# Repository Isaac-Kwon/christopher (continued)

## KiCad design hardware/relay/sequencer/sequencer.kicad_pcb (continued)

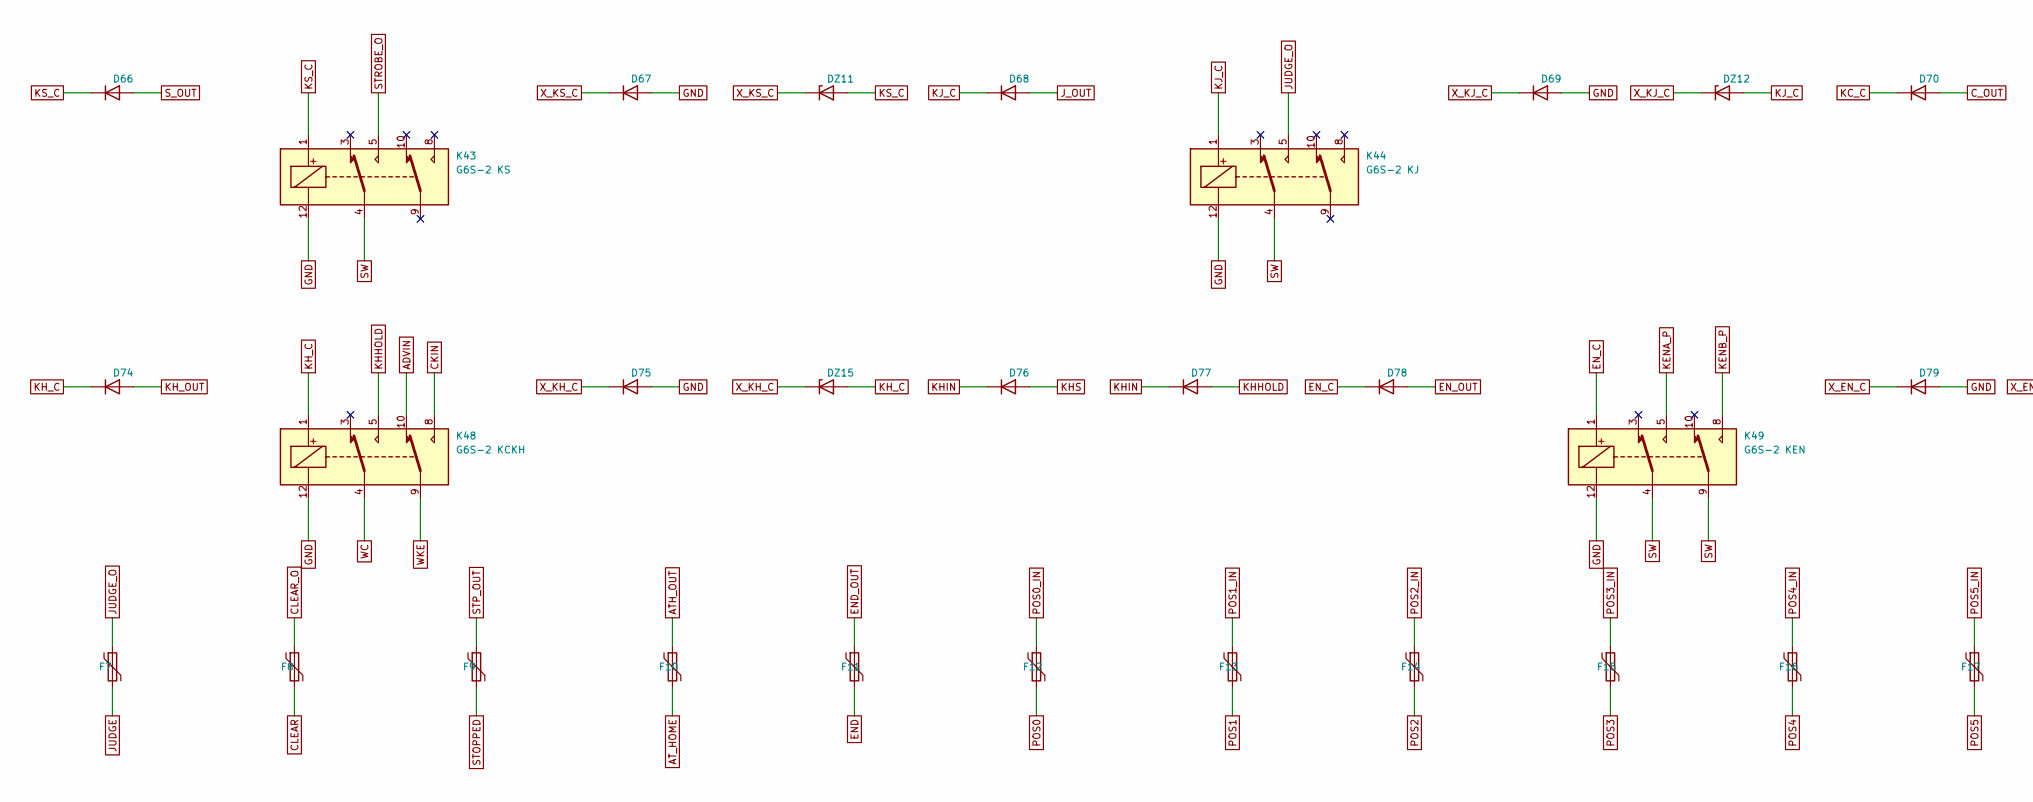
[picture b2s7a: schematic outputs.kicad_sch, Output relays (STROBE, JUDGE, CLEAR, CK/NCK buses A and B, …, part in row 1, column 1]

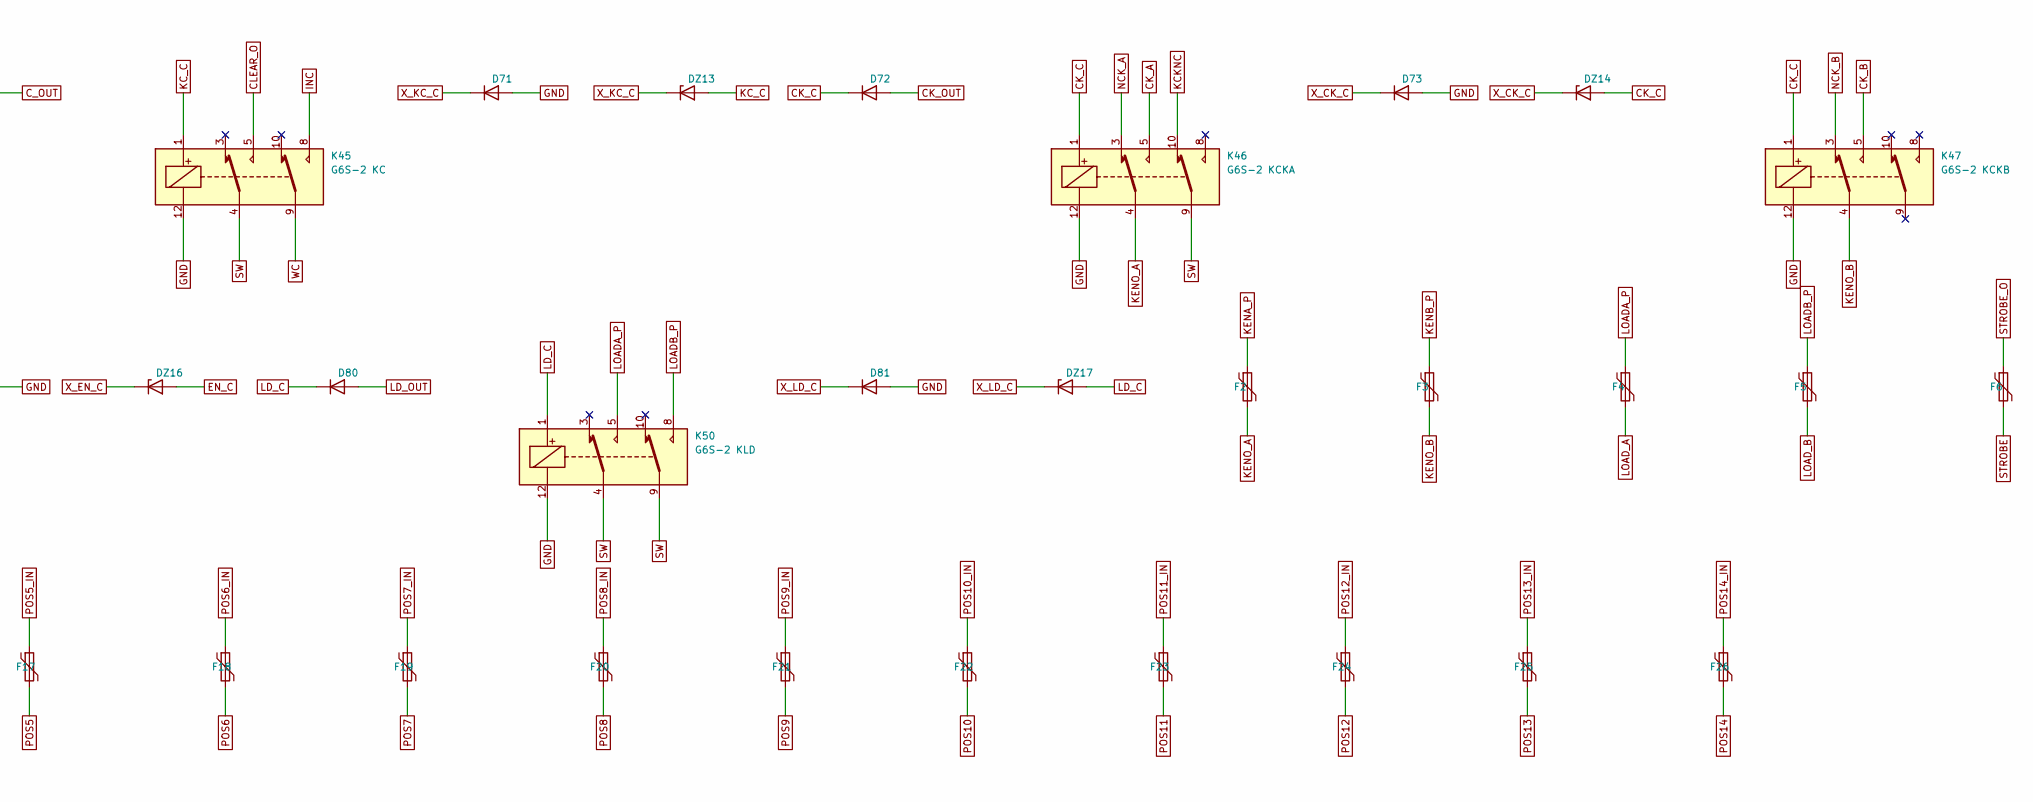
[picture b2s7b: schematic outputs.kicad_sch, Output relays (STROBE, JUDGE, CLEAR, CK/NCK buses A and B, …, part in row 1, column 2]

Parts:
D66, D67, D68, D69, D70, D71, D72, D73, D74, D75, D76, D77, D78, D79, D80, D81: 1N4148W; D_SOD-123
DZ11, DZ12, DZ13, DZ14, DZ15, DZ16, DZ17: BZT52C30; D_SOD-123
F2, F3: PTC 1.1A hold; Fuse_1812_4532Metric
F4, F5: PTC 0.1A hold; Fuse_1206_3216Metric
F6, F7, F8, F9, F10, F11, F12, F13, F14, F15, F16, F17, F18, F19, F20, F21, F22, F23, F24, F25, F26: PTC 30mA hold / 100mA trip; Fuse_1206_3216Metric
K43: G6S-2 KS; Relay_DPDT_Omron_G6S-2
K44: G6S-2 KJ; Relay_DPDT_Omron_G6S-2
K45: G6S-2 KC; Relay_DPDT_Omron_G6S-2
K46: G6S-2 KCKA; Relay_DPDT_Omron_G6S-2
K47: G6S-2 KCKB; Relay_DPDT_Omron_G6S-2
K48: G6S-2 KCKH; Relay_DPDT_Omron_G6S-2
K49: G6S-2 KEN; Relay_DPDT_Omron_G6S-2
K50: G6S-2 KLD; Relay_DPDT_Omron_G6S-2

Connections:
ADVIN: K48.10; also elsewhere on the board
ATH_OUT: F10.1; also elsewhere on the board
AT_HOME: F10.2; also elsewhere on the board
CKIN: K48.8; also elsewhere on the board
CK_A: K46.5; also elsewhere on the board
CK_B: K47.5; also elsewhere on the board
CK_C: D72.1 (K), DZ14.2 (A), K46.1, K47.1
CK_OUT: D72.2 (A); also elsewhere on the board
CLEAR: F8.2; also elsewhere on the board
CLEAR_O: F8.1, K45.5
C_OUT: D70.2 (A); also elsewhere on the board
END: F11.2; also elsewhere on the board
END_OUT: F11.1; also elsewhere on the board
EN_C: D78.1 (K), DZ16.2 (A), K49.1
EN_OUT: D78.2 (A); also elsewhere on the board
GND: D67.2 (A), D69.2 (A), D71.2 (A), D73.2 (A), D75.2 (A), D79.2 (A), D81.2 (A), K43.12, K44.12, K45.12, K46.12, K47.12, K48.12, K49.12, K50.12; also elsewhere on the board
INC: K45.8; also elsewhere on the board
JUDGE: F7.2; also elsewhere on the board
JUDGE_O: F7.1, K44.5
J_OUT: D68.2 (A); also elsewhere on the board
KCKNC: K46.10; also elsewhere on the board
KC_C: D70.1 (K), DZ13.2 (A), K45.1
KENA_P: F2.1, K49.5
KENB_P: F3.1, K49.8
KENO_A: F2.2, K46.4
KENO_B: F3.2, K47.4
KHHOLD: D77.2 (A), K48.5
KHIN: D76.1 (K), D77.1 (K); also elsewhere on the board
KHS: D76.2 (A); also elsewhere on the board
KH_C: D74.1 (K), DZ15.2 (A), K48.1
KH_OUT: D74.2 (A); also elsewhere on the board
KJ_C: D68.1 (K), DZ12.2 (A), K44.1
KS_C: D66.1 (K), DZ11.2 (A), K43.1
LD_C: D80.1 (K), DZ17.2 (A), K50.1
LD_OUT: D80.2 (A); also elsewhere on the board
LOADA_P: F4.1, K50.5
LOADB_P: F5.1, K50.8
LOAD_A: F4.2; also elsewhere on the board
LOAD_B: F5.2; also elsewhere on the board
NCK_A: K46.3; also elsewhere on the board
NCK_B: K47.3; also elsewhere on the board
POS0: F12.2; also elsewhere on the board
POS0_IN: F12.1; also elsewhere on the board
POS1: F13.2; also elsewhere on the board
POS1_IN: F13.1; also elsewhere on the board
POS2: F14.2; also elsewhere on the board
POS2_IN: F14.1; also elsewhere on the board
POS3: F15.2; also elsewhere on the board
POS3_IN: F15.1; also elsewhere on the board
POS4: F16.2; also elsewhere on the board
POS4_IN: F16.1; also elsewhere on the board
POS5: F17.2; also elsewhere on the board
POS5_IN: F17.1; also elsewhere on the board
POS6: F18.2; also elsewhere on the board
POS6_IN: F18.1; also elsewhere on the board
POS7: F19.2; also elsewhere on the board
POS7_IN: F19.1; also elsewhere on the board
POS8: F20.2; also elsewhere on the board
POS8_IN: F20.1; also elsewhere on the board
POS9: F21.2; also elsewhere on the board
POS9_IN: F21.1; also elsewhere on the board
POS10: F22.2; also elsewhere on the board
POS10_IN: F22.1; also elsewhere on the board
POS11: F23.2; also elsewhere on the board
POS11_IN: F23.1; also elsewhere on the board
POS12: F24.2; also elsewhere on the board
POS12_IN: F24.1; also elsewhere on the board
POS13: F25.2; also elsewhere on the board
POS13_IN: F25.1; also elsewhere on the board
POS14: F26.2; also elsewhere on the board
POS14_IN: F26.1; also elsewhere on the board
STOPPED: F9.2; also elsewhere on the board
STP_OUT: F9.1; also elsewhere on the board
STROBE: F6.2; also elsewhere on the board
STROBE_O: F6.1, K43.5
SW: K43.4, K44.4, K45.4, K46.9, K49.4, K49.9, K50.4, K50.9; also elsewhere on the board
S_OUT: D66.2 (A); also elsewhere on the board
WC: K45.9, K48.4; also elsewhere on the board
WKE: K48.9; also elsewhere on the board
X_CK_C: D73.1 (K), DZ14.1 (K)
X_EN_C: D79.1 (K), DZ16.1 (K)
X_KC_C: D71.1 (K), DZ13.1 (K)
X_KH_C: D75.1 (K), DZ15.1 (K)
X_KJ_C: D69.1 (K), DZ12.1 (K)
X_KS_C: D67.1 (K), DZ11.1 (K)
X_LD_C: D81.1 (K), DZ17.1 (K)

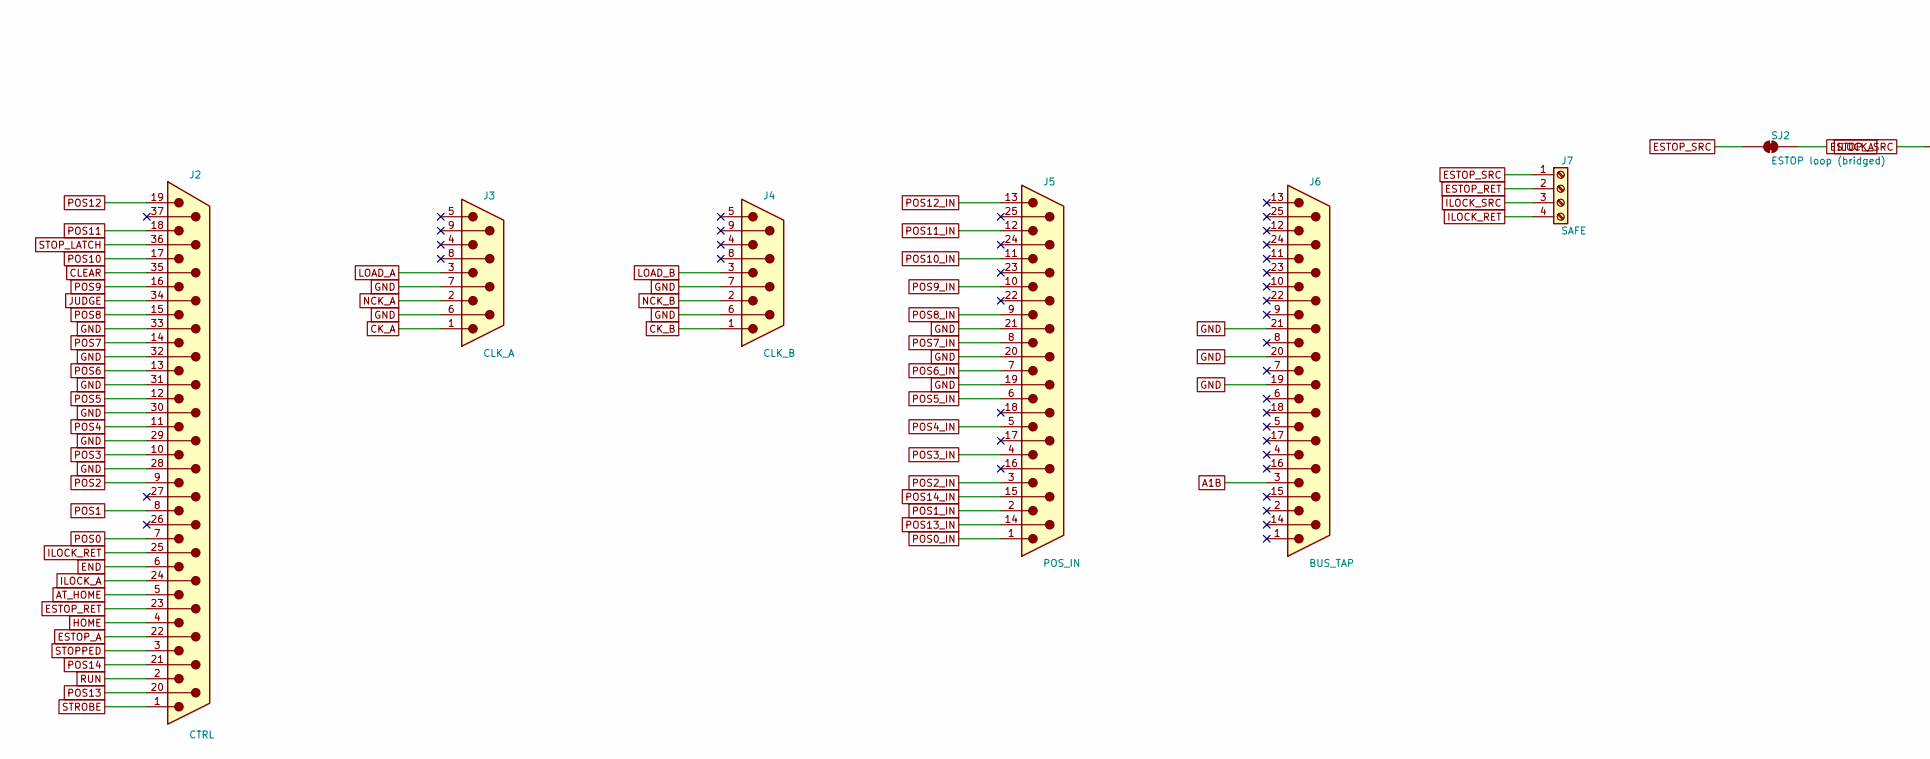
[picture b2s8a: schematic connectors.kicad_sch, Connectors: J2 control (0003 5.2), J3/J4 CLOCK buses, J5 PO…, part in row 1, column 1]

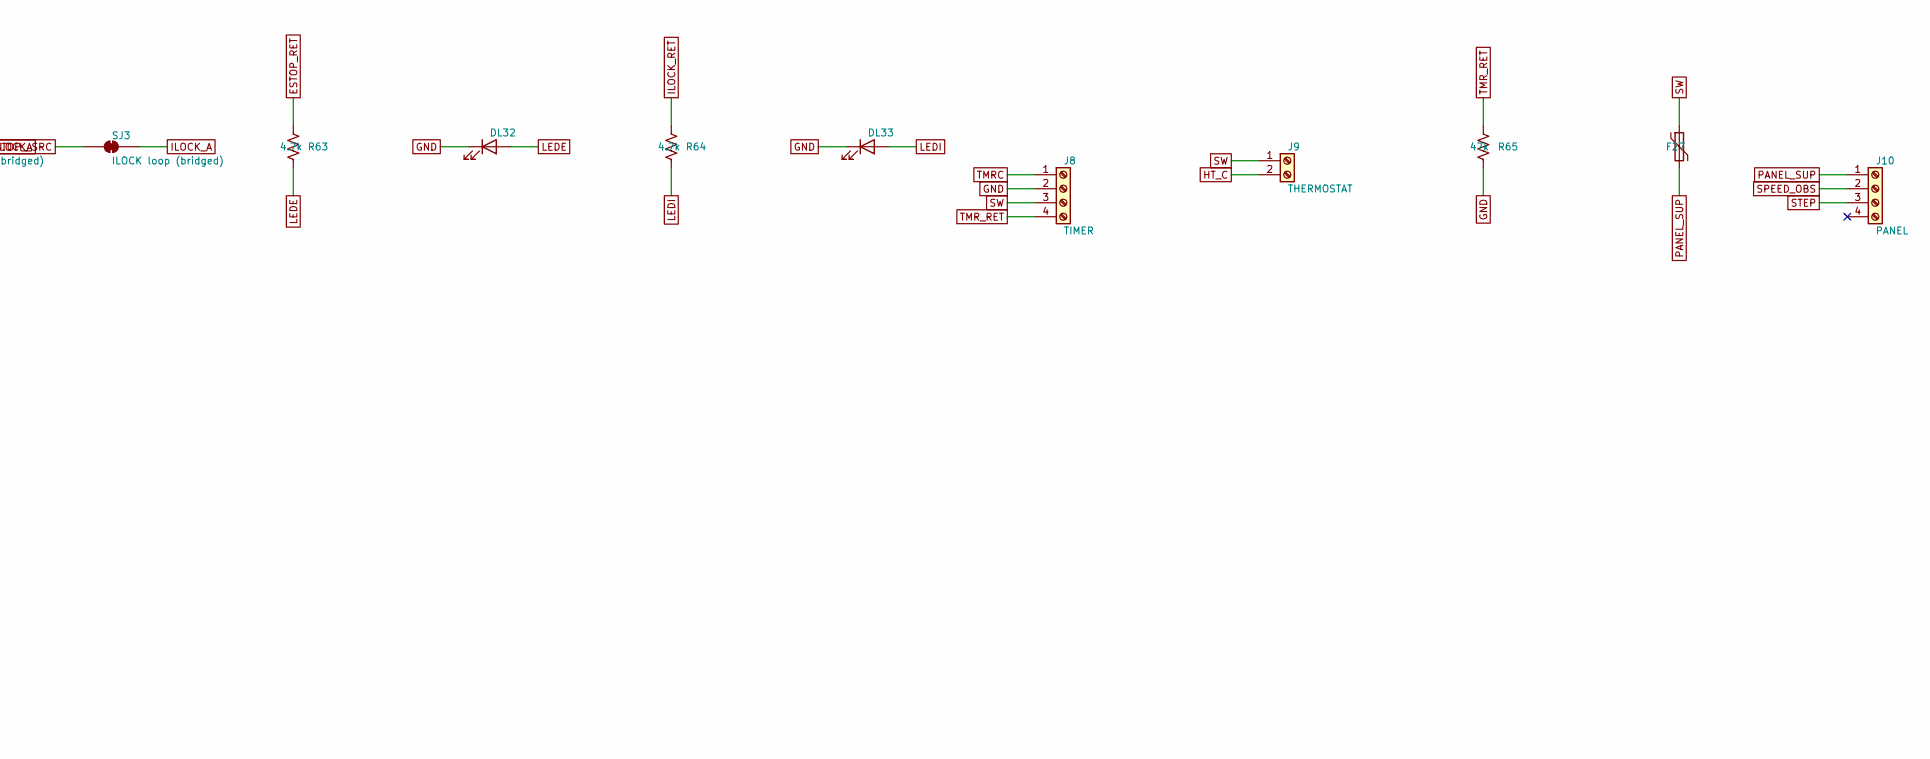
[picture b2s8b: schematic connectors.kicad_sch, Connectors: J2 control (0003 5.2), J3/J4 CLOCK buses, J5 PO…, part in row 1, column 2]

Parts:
DL32: ESTOP loop closed; LED_0603_1608Metric
DL33: ILOCK loop closed; LED_0603_1608Metric
F27: PTC 0.1A hold; Fuse_1206_3216Metric
J2: CTRL; DSUB-37_Pins_Horizontal_P2.77x2.84mm_EdgePinOffset9.90mm_Ho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
J3: CLK_A; DSUB-9_Pins_Horizontal_P2.77x2.84mm_EdgePinOffset9.90mm_Hou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
J4: CLK_B; DSUB-9_Pins_Horizontal_P2.77x2.84mm_EdgePinOffset9.90mm_Hou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
J5: POS_IN; DSUB-25_Pins_Horizontal_P2.77x2.84mm_EdgePinOffset9.90mm_Ho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
J6: BUS_TAP; DSUB-25_Pins_Horizontal_P2.77x2.84mm_EdgePinOffset9.90mm_Ho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
J7: SAFE; TerminalBlock_Phoenix_MKDS-1,5-4-5.08_1x04_P5.08mm_Horizont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
J8: TIMER; TerminalBlock_Phoenix_MKDS-1,5-4-5.08_1x04_P5.08mm_Horizont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
J9: THERMOSTAT; TerminalBlock_Phoenix_MKDS-1,5-2-5.08_1x02_P5.08mm_Horizont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
J10: PANEL; TerminalBlock_Phoenix_MKDS-1,5-4-5.08_1x04_P5.08mm_Horizont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
R63, R64: 4.7k; R_0603_1608Metric
R65: 47k; R_0603_1608Metric
SJ2: ESTOP loop (bridged); SolderJumper-2_P1.3mm_Bridged_RoundedPad1.0x1.5mm
SJ3: ILOCK loop (bridged); SolderJumper-2_P1.3mm_Bridged_RoundedPad1.0x1.5mm

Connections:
A1B: J6.3; also elsewhere on the board
AT_HOME: J2.5; also elsewhere on the board
CHASSIS: J2.SH, J3.SH, J4.SH, J5.SH, J6.SH; also elsewhere on the board
CK_A: J3.1; also elsewhere on the board
CK_B: J4.1; also elsewhere on the board
CLEAR: J2.35; also elsewhere on the board
END: J2.6; also elsewhere on the board
ESTOP_A: J2.22, SJ2.2 (B)
ESTOP_RET: J2.23, J7.2, R63.1
ESTOP_SRC: J7.1, SJ2.1 (A)
GND: DL32.1 (K), DL33.1 (K), J2.28, J2.29, J2.30, J2.31, J2.32, J2.33, J3.6, J3.7, J4.6, J4.7, J5.19, J5.20, J5.21, J6.19, J6.20, J6.21, J8.2, R65.2; also elsewhere on the board
HOME: J2.4; also elsewhere on the board
HT_C: J9.2; also elsewhere on the board
ILOCK_A: J2.24, SJ3.2 (B)
ILOCK_RET: J2.25, J7.4, R64.1
ILOCK_SRC: J7.3, SJ3.1 (A)
JUDGE: J2.34; also elsewhere on the board
LEDE: DL32.2 (A), R63.2
LEDI: DL33.2 (A), R64.2
LOAD_A: J3.3; also elsewhere on the board
LOAD_B: J4.3; also elsewhere on the board
NCK_A: J3.2; also elsewhere on the board
NCK_B: J4.2; also elsewhere on the board
PANEL_SUP: F27.2, J10.1
POS0: J2.7; also elsewhere on the board
POS0_IN: J5.1; also elsewhere on the board
POS1: J2.8; also elsewhere on the board
POS1_IN: J5.2; also elsewhere on the board
POS2: J2.9; also elsewhere on the board
POS2_IN: J5.3; also elsewhere on the board
POS3: J2.10; also elsewhere on the board
POS3_IN: J5.4; also elsewhere on the board
POS4: J2.11; also elsewhere on the board
POS4_IN: J5.5; also elsewhere on the board
POS5: J2.12; also elsewhere on the board
POS5_IN: J5.6; also elsewhere on the board
POS6: J2.13; also elsewhere on the board
POS6_IN: J5.7; also elsewhere on the board
POS7: J2.14; also elsewhere on the board
POS7_IN: J5.8; also elsewhere on the board
POS8: J2.15; also elsewhere on the board
POS8_IN: J5.9; also elsewhere on the board
POS9: J2.16; also elsewhere on the board
POS9_IN: J5.10; also elsewhere on the board
POS10: J2.17; also elsewhere on the board
POS10_IN: J5.11; also elsewhere on the board
POS11: J2.18; also elsewhere on the board
POS11_IN: J5.12; also elsewhere on the board
POS12: J2.19; also elsewhere on the board
POS12_IN: J5.13; also elsewhere on the board
POS13: J2.20; also elsewhere on the board
POS13_IN: J5.14; also elsewhere on the board
POS14: J2.21; also elsewhere on the board
POS14_IN: J5.15; also elsewhere on the board
RUN: J2.2; also elsewhere on the board
SPEED_OBS: J10.2; also elsewhere on the board
STEP: J10.3; also elsewhere on the board
STOPPED: J2.3; also elsewhere on the board
STOP_LATCH: J2.36; also elsewhere on the board
STROBE: J2.1; also elsewhere on the board
SW: F27.1, J8.3, J9.1; also elsewhere on the board
TMRC: J8.1; also elsewhere on the board
TMR_RET: J8.4, R65.1; also elsewhere on the board

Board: 4 copper layers, 309 parts (0 on the bottom side), 247 nets, no tracks yet.
